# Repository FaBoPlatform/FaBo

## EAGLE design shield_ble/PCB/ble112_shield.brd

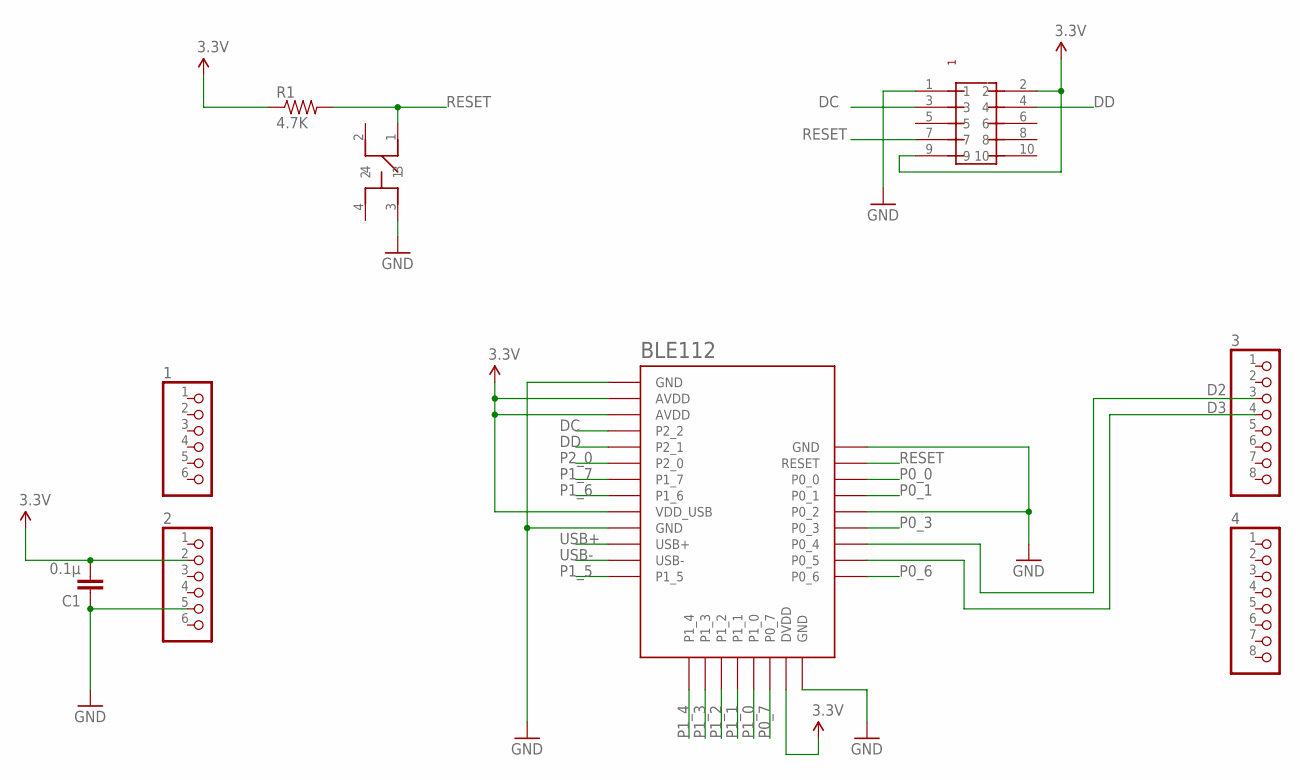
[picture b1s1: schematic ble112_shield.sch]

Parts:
1, 2: PINHD-1X6CB; 1X06-CLEANBIG
3, 4: PINHD-1X8CLEANBIG; 1X08-CLEANBIG
BLE112: SF-BLUEGIGA_BLE112-A-VISUAL; SF-BLUEGIGA_BLE112-A
C1: 0.1μ; 0603-CAP
R1: 4.7K; 0603-RES
U$1: PIN-HEADER-SMT(1.27MM)2X5
U$4: SWITCH-LS6J2M-T; SWICTH-LS6J2M-T

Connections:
3.3V: 2.2, BLE112.AVDD1 (AVDD), BLE112.AVDD2 (AVDD), BLE112.DVDD, BLE112.VDD_USB, C1.2, R1.1, U$1.2, U$1.9
D2: 3.3, BLE112.P0_4
D3: 3.4, BLE112.P0_5
DC: BLE112.P2_2, U$1.3
DD: BLE112.P2_1, U$1.4
GND: 2.5, BLE112.GND1 (GND), BLE112.GND2 (GND), BLE112.GND3 (GND), BLE112.GND4 (GND), BLE112.P0_2, C1.1, U$1.1, U$4.3
P0_0: BLE112.P0_0
P0_1: BLE112.P0_1
P0_3: BLE112.P0_3
P0_6: BLE112.P0_6
P0_7: BLE112.P0_7
P1_0: BLE112.P1_0
P1_1: BLE112.P1_1
P1_2: BLE112.P1_2
P1_3: BLE112.P1_3
P1_4: BLE112.P1_4
P1_5: BLE112.P1_5
P1_6: BLE112.P1_6
P1_7: BLE112.P1_7
P2_0: BLE112.P2_0
RESET: BLE112.RESET, R1.2, U$1.7, U$4.1
USB+: BLE112.USB+
USB-: BLE112.USB-

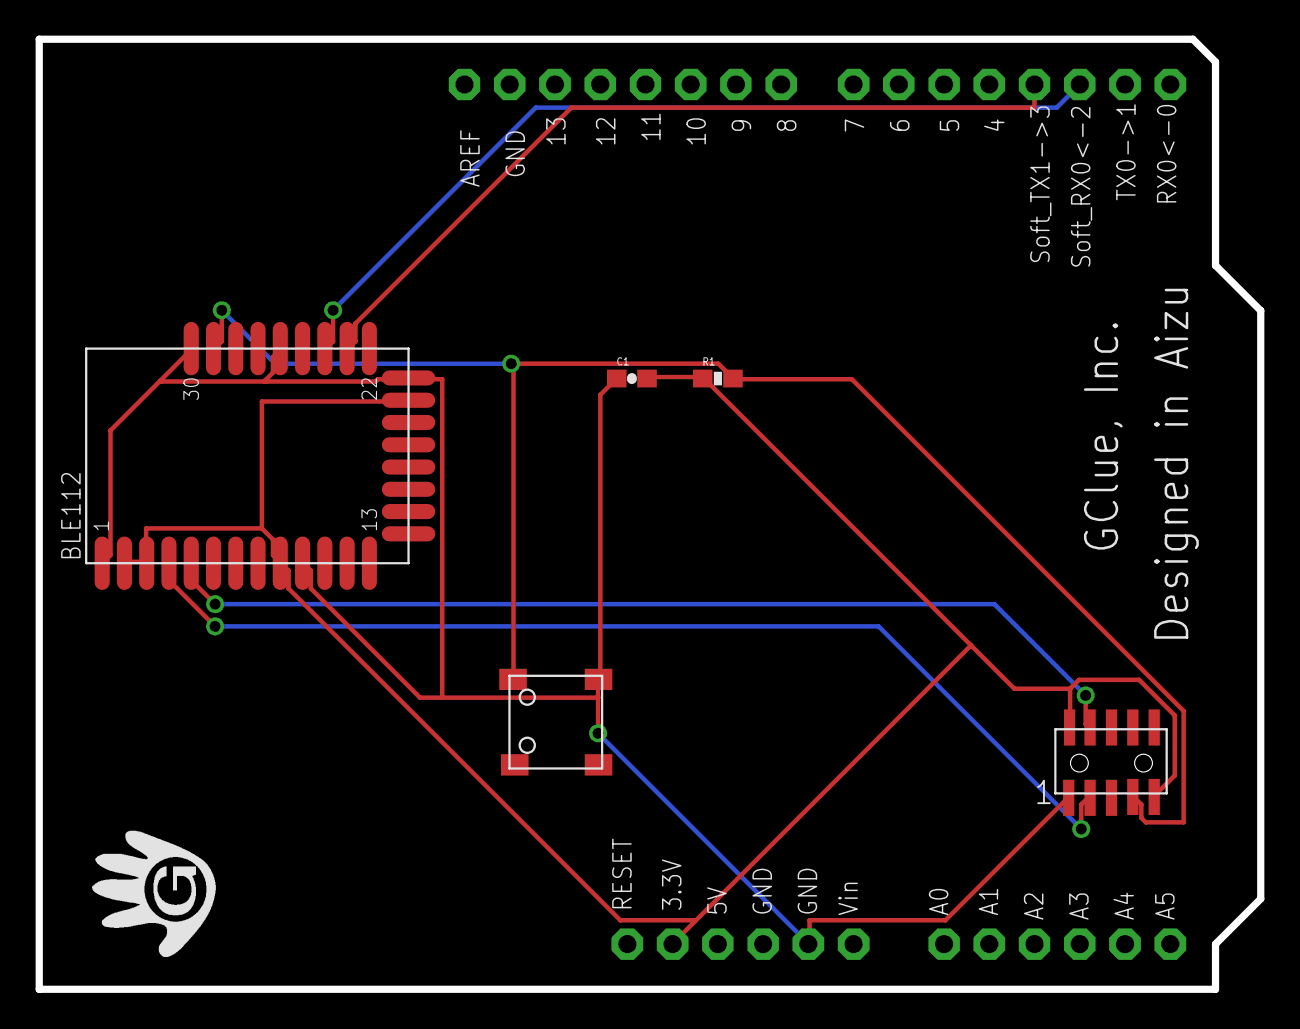
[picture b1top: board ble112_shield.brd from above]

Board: 2 copper layers, 68.6 x 53.3 mm, 9 parts (0 on the bottom side), 7 nets.

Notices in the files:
parts and their libraries:
SparkFun: Licensing: CC v3.0 Share-Alike You are welcome to use this library for commercial purposes.
